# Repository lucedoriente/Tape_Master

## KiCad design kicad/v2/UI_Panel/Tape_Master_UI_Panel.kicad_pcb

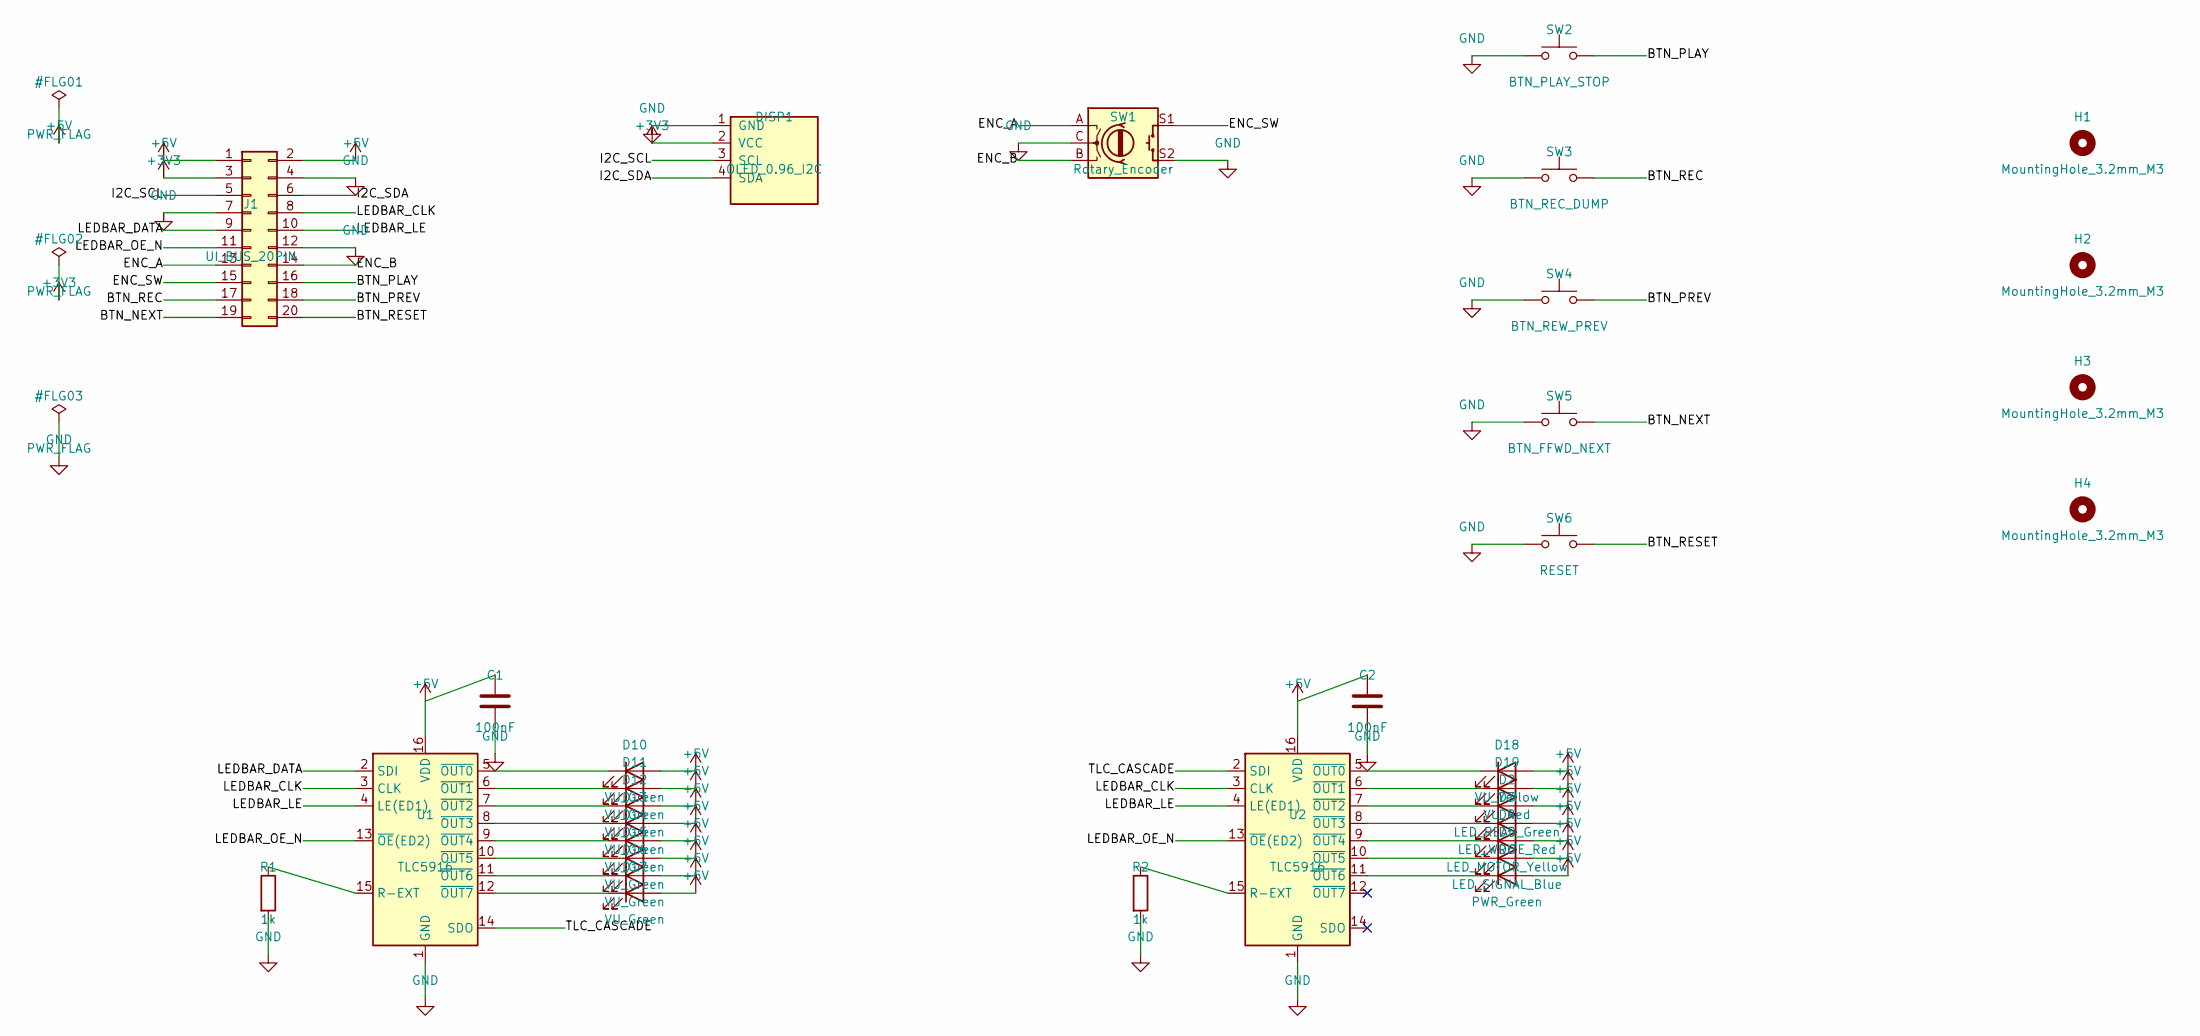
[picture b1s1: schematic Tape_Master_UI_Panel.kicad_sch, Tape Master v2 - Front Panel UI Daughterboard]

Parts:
C1, C2: 100nF; C_0805_2012Metric
D2: LED_READ_Green; LED_0805_2012Metric
D3: LED_WRITE_Red; LED_0805_2012Metric
D4: LED_MOTOR_Yellow; LED_0805_2012Metric
D5: LED_SIGNAL_Blue; LED_0805_2012Metric
D6: PWR_Green; LED_0805_2012Metric
D10, D11, D12, D13, D14, D15, D16, D17: VU_Green; LED_0805_2012Metric
D18: VU_Yellow; LED_0805_2012Metric
D19: VU_Red; LED_0805_2012Metric
DISP1: OLED_0.96_I2C; PinHeader_1x04_P2.54mm_Vertical
H1, H2, H3, H4: MountingHole_3.2mm_M3
J1: UI_BUS_20PIN; IDC-Header_2x10_P2.54mm_Vertical
R1, R2: 1k; R_0805_2012Metric
SW1: Rotary_Encoder; RotaryEncoder_Alps_EC11E-Switch_Vertical_H20mm
SW2: BTN_PLAY_STOP; SW_PUSH_6mm
SW3: BTN_REC_DUMP; SW_PUSH_6mm
SW4: BTN_REW_PREV; SW_PUSH_6mm
SW5: BTN_FFWD_NEXT; SW_PUSH_6mm
SW6: RESET; SW_PUSH_6mm
U1, U2: TLC5916; SOIC-16_3.9x9.9mm_P1.27mm

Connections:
+3V3: DISP1.2 (VCC), J1.3
+5V: C1.1, C2.1, D2.2 (A), D3.2 (A), D4.2 (A), D5.2 (A), D6.2 (A), D10.2 (A), D11.2 (A), D12.2 (A), D13.2 (A), D14.2 (A), D15.2 (A), D16.2 (A), D17.2 (A), D18.2 (A), D19.2 (A), J1.1, J1.2, U1.16 (VDD), U2.16 (VDD)
/BTN_NEXT: J1.19, SW5.2
/BTN_PLAY: J1.16, SW2.2
/BTN_PREV: J1.18, SW4.2
/BTN_REC: J1.17, SW3.2
/BTN_RESET: J1.20, SW6.2
/ENC_A: J1.13, SW1.A
/ENC_B: J1.14, SW1.B
/ENC_SW: J1.15, SW1.S1
/I2C_SCL: DISP1.3 (SCL), J1.5
/I2C_SDA: DISP1.4 (SDA), J1.6
/LEDBAR_CLK: J1.8, U1.3 (CLK), U2.3 (CLK)
/LEDBAR_DATA: J1.9, U1.2 (SDI)
/LEDBAR_LE: J1.10, U1.4 (LE(ED1)), U2.4 (LE(ED1))
/LEDBAR_OE_N: J1.11, U1.13 (~OE(ED2)), U2.13 (~OE(ED2))
/TLC_CASCADE: U1.14 (SDO), U2.2 (SDI)
GND: C1.2, C2.2, DISP1.1 (GND), J1.4, J1.7, J1.12, R1.2, R2.2, SW1.C, SW1.S2, SW2.1, SW3.1, SW4.1, SW5.1, SW6.1, U1.1 (GND), U2.1 (GND)
unnamed: D2.1 (K), U2.7 (~OUT2)
unnamed: D3.1 (K), U2.8 (~OUT3)
unnamed: D4.1 (K), U2.9 (~OUT4)
unnamed: D5.1 (K), U2.10 (~OUT5)
unnamed: D6.1 (K), U2.11 (~OUT6)
unnamed: D10.1 (K), U1.5 (~OUT0)
unnamed: D11.1 (K), U1.6 (~OUT1)
unnamed: D12.1 (K), U1.7 (~OUT2)
unnamed: D13.1 (K), U1.8 (~OUT3)
unnamed: D14.1 (K), U1.9 (~OUT4)
unnamed: D15.1 (K), U1.10 (~OUT5)
unnamed: D16.1 (K), U1.11 (~OUT6)
unnamed: D17.1 (K), U1.12 (~OUT7)
unnamed: D18.1 (K), U2.5 (~OUT0)
unnamed: D19.1 (K), U2.6 (~OUT1)
unnamed: R1.1, U1.15 (R-EXT)
unnamed: R2.1, U2.15 (R-EXT)

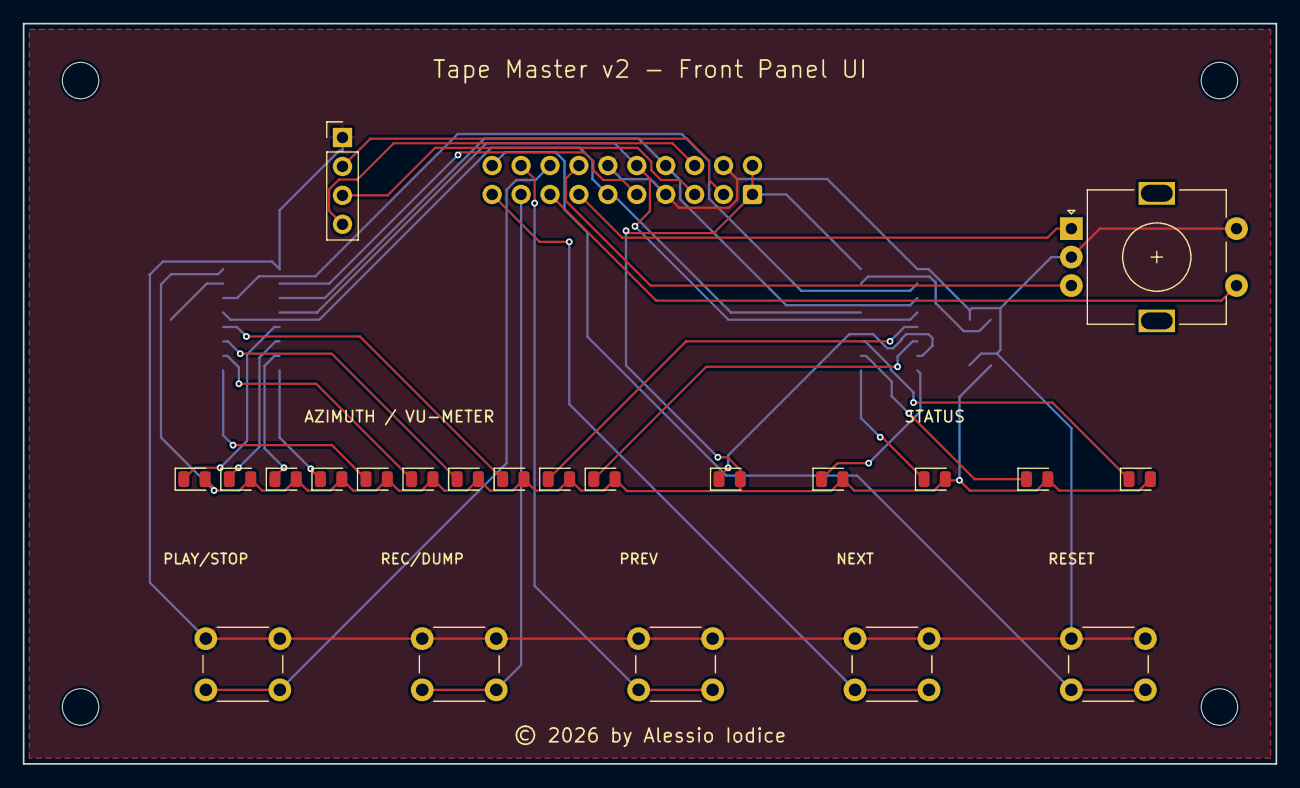
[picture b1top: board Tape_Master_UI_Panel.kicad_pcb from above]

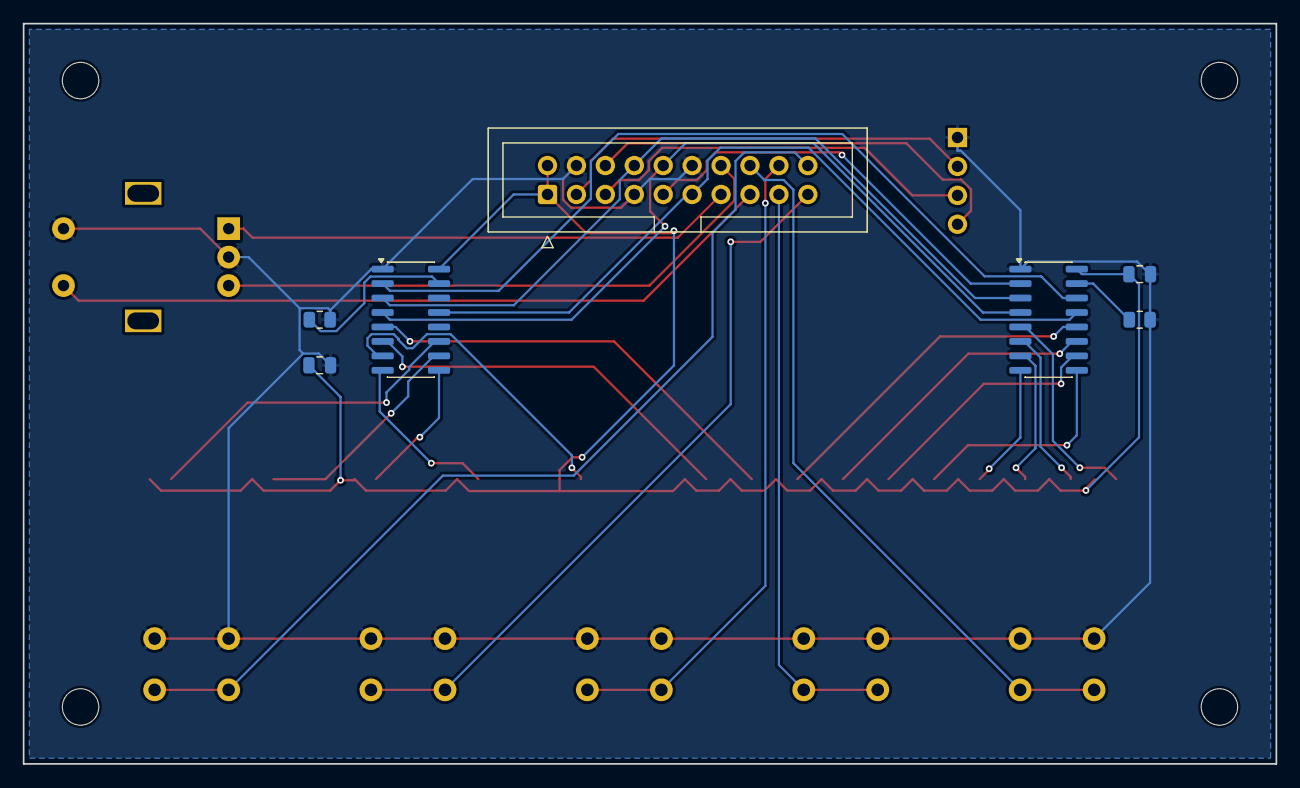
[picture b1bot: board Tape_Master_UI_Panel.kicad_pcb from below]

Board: 2 copper layers, 110.0 x 65.0 mm, 33 parts (7 on the bottom side), 35 nets.

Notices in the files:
kicad/v2/UI_Panel/Tape_Master_UI_Panel.kicad_pcb:
License: CC BY-NC-SA 4.0
© 2026 by Alessio Iodice
